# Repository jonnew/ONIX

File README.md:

# NOTE: This repository has been split into individual `onix-<project>` repos that are hosted on the [open-ephys github account](https://github.com/open-ephys). This repo has been archived.

[ONIX](https://open-ephys.github.io/onix-docs/index.html) is a collection
of [ONI](https://github.com/jonnew/ONI)-compatible hardware and API
for serialized, very-high channel count, closed-loop electrophysiology. It is
an evolution of the first-generation hardware and software introduced in [Open
Ephys project](http://www.open-ephys.org/) and involves many of the same
developers.  The firmware and API are general purpose -- they can be used to
acquire from and control custom headstages with arbitrary arrangements of
sensors and actuators (e.g. cameras, bioamplifier chips, LED drivers, etc.) and
are not limited to the hardware in this repository.

__Documentation__ : https://open-ephys.github.io/onix-docs/index.html

__Citing this work__: 

1. Citing the paper

  - TODO

2. Citing the repository itself

  - 

## Features
- Follows the [ONI](https://github.com/jonnew/ONI)-specification for serialization protocols, host communication
  protocols, device drivers, and host API
- Firmware and API permit acquisition and control of arbitrary arrangements of
  sensors and actuators:

    - Headstages
    - Miniscopes
    - Photometry systems
    - Etc.

- Submillisecond round-trip communication from brain, through host PC's main
  memory, and back again.
- Headstages:

    - 64-, 128-, 256-channels of electrophysiology
    - Optogenetic stimulation
    - Electrical stimulation
    - 3D-pose measurement
    - Data, user control, and power via a tiny coaxial cable
    - Wireless communication

- Low-level API implementation
- High-level API language bindings and existing integration with [Open Ephys
  GUI](http://www.open-ephys.org/gui/) and [Bonsai](http://bonsai-rx.org/).
- Quality documentation and easy routes to purchasing assembled devices.

## Software

1. API: https://github.com/jonnew/liboni
2. Bonsai package: coming soon
3. Open Ephys GUI plugin: coming soon

## Hardware

### [eib-64](eib-64/README.md)
64 Channel electrode interface board. Designed for small rodent tetrode
electrophysiology. Works with [headstage-64](./headstage-64/README.md).

### [eib-128](eib-128/README.md)
128 Channel electrode interface board. Designed for large rodent tetrode
electrophysiology. Works with [headstage-256](./headstage-256/README.md).

### [eib-256](eib-256/README.md)
256 Channel electrode interface board. Designed for large rodent tetrode
electrophysiology. Works with [headstage-256](./headstage-256/README.md).

### [headstage-64](headstage-64/README.md)
Serialized, multifunction headstage for small rodents. Supports 64 channels.
Designed to interface with [eib-64](./eib-64/README.md).

### [headstage-256](headstage-256/README.md)
Serialized, multifunction headstage for large rodents. Supports both 128 or 256
channels. Designed to interface with [eib-128](./eib-128/README.md) or
[eib-256](./eib-256/README.md)

### [fmc-host](fmc-host/README.md)
Base board for facilitating PCIe communication, via FMC compatiable and
PCIe-capable FPGA based board (e.g. [Numato Lab
Nereid](https://numato.com/product/nereid-kintex-7-pci-express-fpga-development-board).
This board plugs into the FMC connector on the base board. It provides
communication with one headstage and lots of other analog and digital IO.

### [analog-io-breakout](analog-io-breakout/README.md)
Passive breakout board for acquiring and generating analog signals through BNC,
SMA, ribbon, or straight wire connections. Plugs into fmc-host using a 26-pin
shrunk delta ribbon cable.

### [nanoz-adapter-64](./nanoz-adapter-64/README.md)
Adapter to interface eib-64 with the popular
[nanoZ](http://www.white-matter.com/nanoz/) electrode impedance tester and
plating device.

### [nanoz-adapter-128-256](./nanoz-adapter-128-256/README.md)
Multiplexed adapter to interface eib-128 and eib-256 with the popular
[nanoZ](http://www.white-matter.com/nanoz/) electrode impedance tester and
plating device.

### [test-board-64](./test-board-64)
Test board for headstage-64. Allows injecting simulated biopotentials into
headstage modules via a selectable passive attenuator. Provides LEDs and
simulated electrical loads for optical and electrical stimulation.

### [test-board-128-256](./test-board-128-256)
Test board for headstage, and headstage-256 modules. Allows injecting simulated
biopotentials into headstage modules via a selectable passive attenuator.
Provides LEDs and simulated electrical loads for optical and electrical
stimulation.

### [headstage-programmer](headstage-programmer/README.md)
JTAG breakout for the [Intel USB Blaster 2](https://www.digikey.com/short/qqw7hm)
used to program the headstages' MAX10 FPGA.

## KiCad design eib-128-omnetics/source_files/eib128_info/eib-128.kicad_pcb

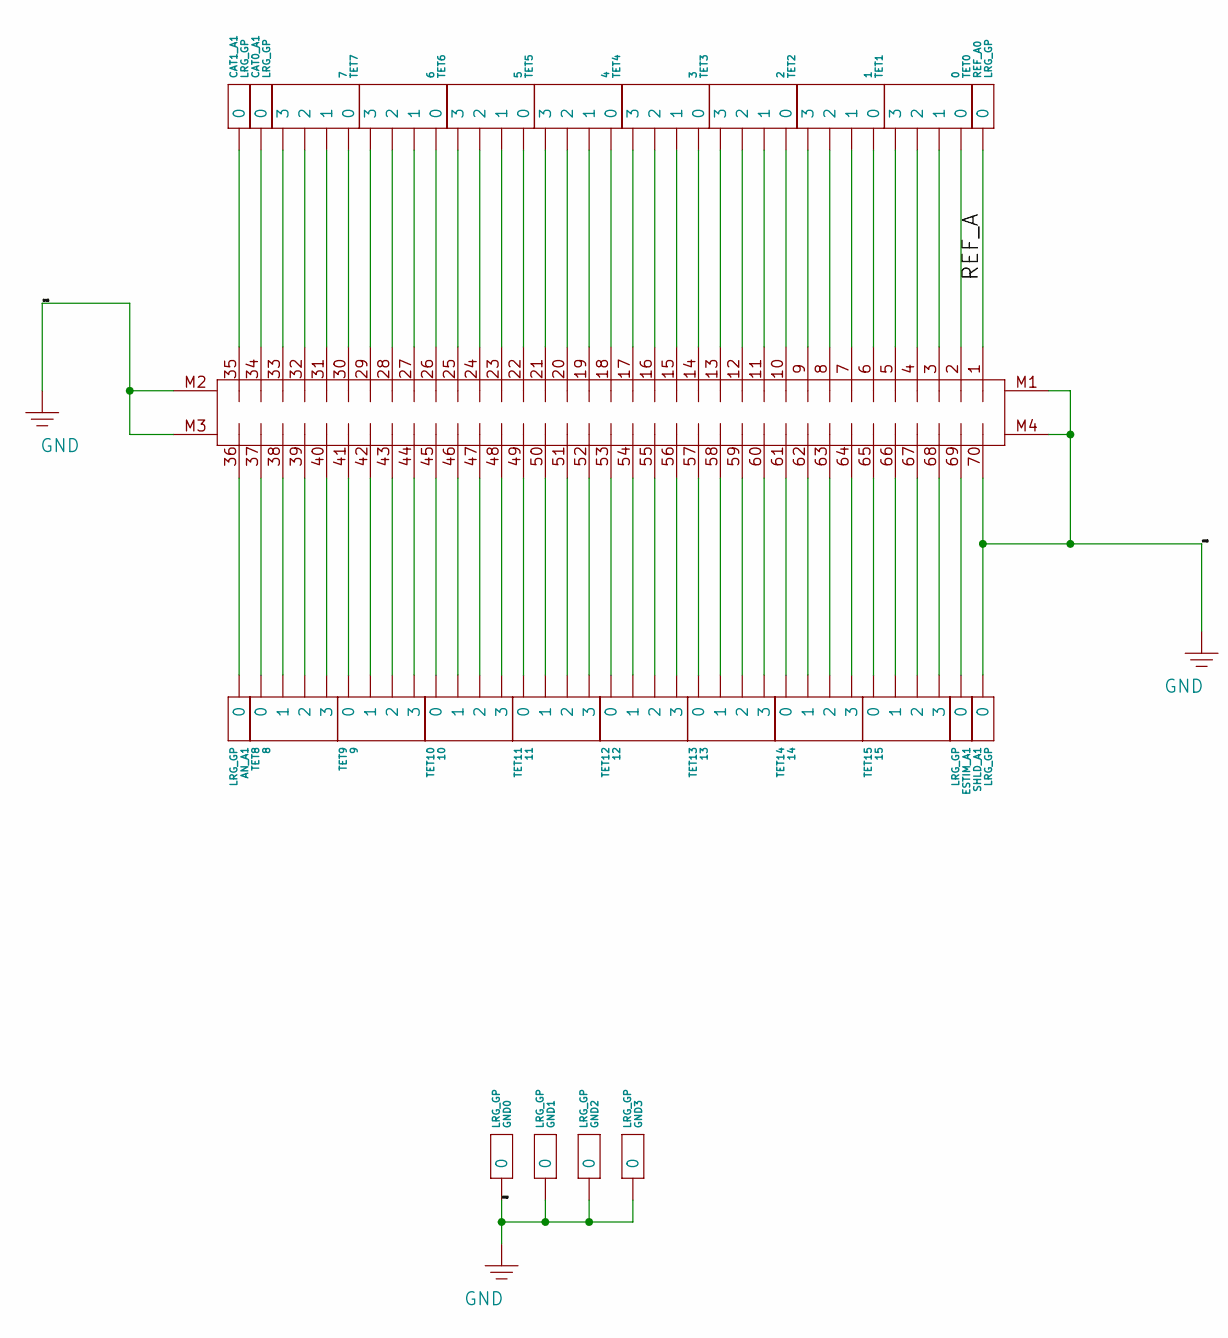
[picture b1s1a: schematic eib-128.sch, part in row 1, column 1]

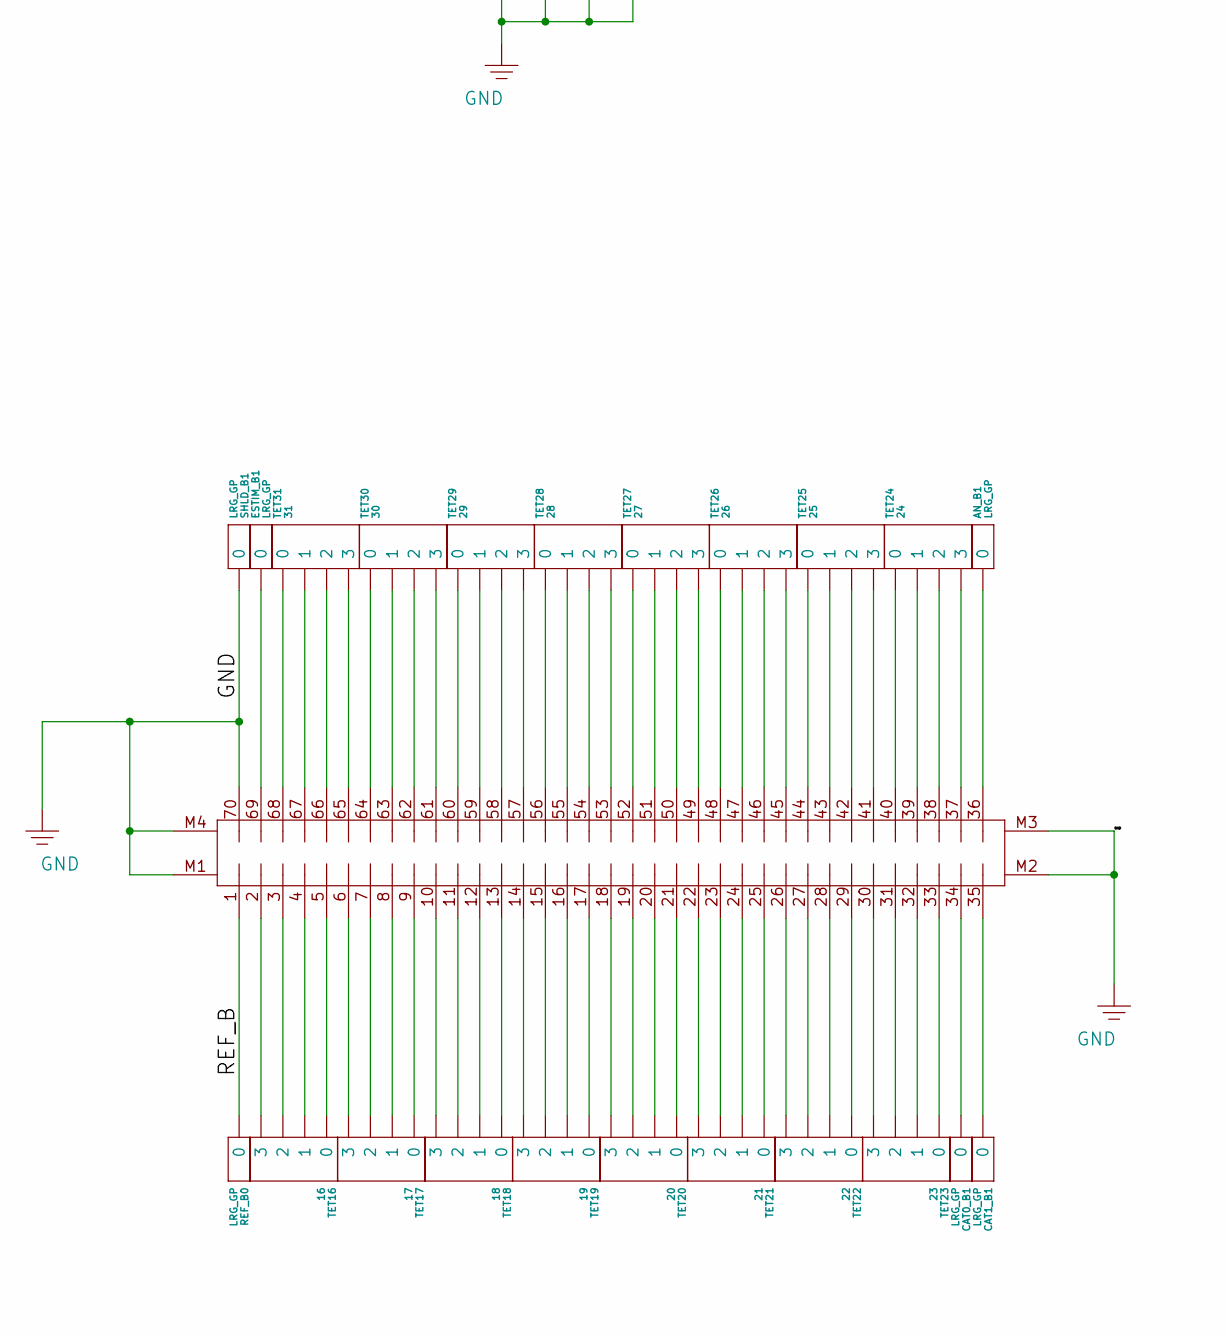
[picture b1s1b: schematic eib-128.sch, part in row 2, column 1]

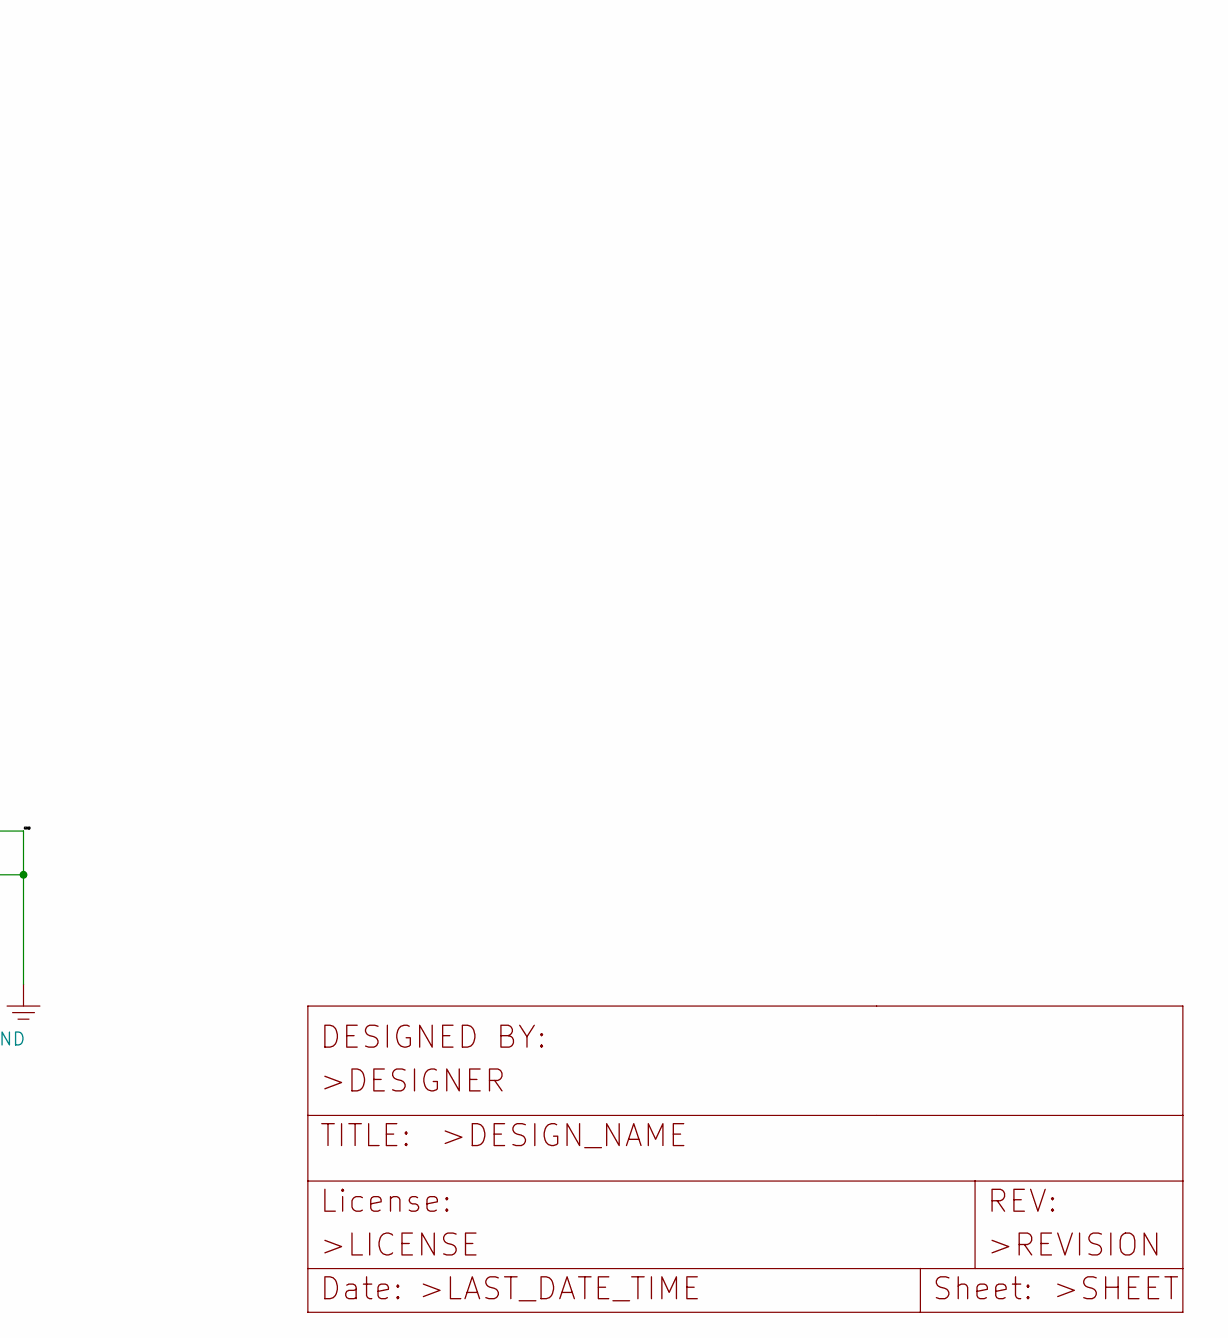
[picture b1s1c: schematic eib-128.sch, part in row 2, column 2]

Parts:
A1: DF40HEAD; DF40-70HEAD
AN_A1: LRG_GP; GOLDPIN_0.5ID_0.7OD
AN_B1: LRG_GP; GOLDPIN_0.5ID_0.7OD
B1: DF40HEAD; DF40-70HEAD
CAT0_A1, CAT0_B1, CAT1_A1, CAT1_B1: LRG_GP; GOLDPIN_0.5ID_0.7OD
ESTIM_A1: LRG_GP; GOLDPIN_0.5ID_0.7OD
ESTIM_B1: LRG_GP; GOLDPIN_0.5ID_0.7OD
GND0, GND1, GND2, GND3: LRG_GP; GOLDPIN_0.5ID_0.7OD
REF_A0: LRG_GP; GOLDPIN_0.5ID_0.7OD
REF_B0: LRG_GP; GOLDPIN_0.5ID_0.7OD
SHLD_A1: LRG_GP; GOLDPIN_0.5ID_0.7OD
SHLD_B1: LRG_GP; GOLDPIN_0.5ID_0.7OD
TET0: 0; TETRODE_128_0.5ID_0.7OD
TET1: 1; TETRODE_128_0.5ID_0.7OD
TET2: 2; TETRODE_128_0.5ID_0.7OD
TET3: 3; TETRODE_128_0.5ID_0.7OD
TET4: 4; TETRODE_128_0.5ID_0.7OD
TET5: 5; TETRODE_128_0.5ID_0.7OD
TET6: 6; TETRODE_128_0.5ID_0.7OD
TET7: 7; TETRODE_128_0.5ID_0.7OD
TET8: 8; TETRODE_128_0.5ID_0.7OD
TET9: 9; TETRODE_128_0.5ID_0.7OD
TET10: 10; TETRODE_128_0.5ID_0.7OD
TET11: 11; TETRODE_128_0.5ID_0.7OD
TET12: 12; TETRODE_128_0.5ID_0.7OD
TET13: 13; TETRODE_128_0.5ID_0.7OD
TET14: 14; TETRODE_128_0.5ID_0.7OD
TET15: 15; TETRODE_128_0.5ID_0.7OD
TET16: 16; TETRODE_128_0.5ID_0.7OD
TET17: 17; TETRODE_128_0.5ID_0.7OD
TET18: 18; TETRODE_128_0.5ID_0.7OD
TET19: 19; TETRODE_128_0.5ID_0.7OD
TET20: 20; TETRODE_128_0.5ID_0.7OD
TET21: 21; TETRODE_128_0.5ID_0.7OD
TET22: 22; TETRODE_128_0.5ID_0.7OD
TET23: 23; TETRODE_128_0.5ID_0.7OD
TET24: 24; TETRODE_128_0.5ID_0.7OD
TET25: 25; TETRODE_128_0.5ID_0.7OD
TET26: 26; TETRODE_128_0.5ID_0.7OD
TET27: 27; TETRODE_128_0.5ID_0.7OD
TET28: 28; TETRODE_128_0.5ID_0.7OD
TET29: 29; TETRODE_128_0.5ID_0.7OD
TET30: 30; TETRODE_128_0.5ID_0.7OD
TET31: 31; TETRODE_128_0.5ID_0.7OD

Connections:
/REF_A: A1.1, REF_A0.P$1
/REF_B: B1.1, REF_B0.P$1
GND: A1.70, A1.M1, A1.M2, A1.M3, A1.M4, B1.70, B1.M1, B1.M2, B1.M3, B1.M4, GND0.P$1, GND1.P$1, GND2.P$1, GND3.P$1, SHLD_A1.P$1, SHLD_B1.P$1
unnamed: A1.2, TET0.0
unnamed: A1.3, TET0.1
unnamed: A1.4, TET0.2
unnamed: A1.5, TET0.3
unnamed: A1.6, TET1.0
unnamed: A1.7, TET1.1
unnamed: A1.8, TET1.2
unnamed: A1.9, TET1.3
unnamed: A1.10, TET2.0
unnamed: A1.11, TET2.1
unnamed: A1.12, TET2.2
unnamed: A1.13, TET2.3
unnamed: A1.14, TET3.0
unnamed: A1.15, TET3.1
unnamed: A1.16, TET3.2
unnamed: A1.17, TET3.3
unnamed: A1.18, TET4.0
unnamed: A1.19, TET4.1
unnamed: A1.20, TET4.2
unnamed: A1.21, TET4.3
unnamed: A1.22, TET5.0
unnamed: A1.23, TET5.1
unnamed: A1.24, TET5.2
unnamed: A1.25, TET5.3
unnamed: A1.26, TET6.0
unnamed: A1.27, TET6.1
unnamed: A1.28, TET6.2
unnamed: A1.29, TET6.3
unnamed: A1.30, TET7.0
unnamed: A1.31, TET7.1
unnamed: A1.32, TET7.2
unnamed: A1.33, TET7.3
unnamed: A1.34, CAT0_A1.P$1
unnamed: A1.35, CAT1_A1.P$1
unnamed: A1.36, AN_A1.P$1
unnamed: A1.37, TET8.0
unnamed: A1.38, TET8.1
unnamed: A1.39, TET8.2
unnamed: A1.40, TET8.3
unnamed: A1.41, TET9.0
unnamed: A1.42, TET9.1
unnamed: A1.43, TET9.2
unnamed: A1.44, TET9.3
unnamed: A1.45, TET10.0
unnamed: A1.46, TET10.1
unnamed: A1.47, TET10.2
unnamed: A1.48, TET10.3
unnamed: A1.49, TET11.0
unnamed: A1.50, TET11.1
unnamed: A1.51, TET11.2
unnamed: A1.52, TET11.3
unnamed: A1.53, TET12.0
unnamed: A1.54, TET12.1
unnamed: A1.55, TET12.2
unnamed: A1.56, TET12.3
unnamed: A1.57, TET13.0
unnamed: A1.58, TET13.1
unnamed: A1.59, TET13.2
unnamed: A1.60, TET13.3
unnamed: A1.61, TET14.0
unnamed: A1.62, TET14.1
unnamed: A1.63, TET14.2
unnamed: A1.64, TET14.3
unnamed: A1.65, TET15.0
unnamed: A1.66, TET15.1
unnamed: A1.67, TET15.2
unnamed: A1.68, TET15.3
unnamed: A1.69, ESTIM_A1.P$1
unnamed: AN_B1.P$1, B1.36
unnamed: B1.2, TET16.3
unnamed: B1.3, TET16.2
unnamed: B1.4, TET16.1
unnamed: B1.5, TET16.0
unnamed: B1.6, TET17.3
unnamed: B1.7, TET17.2
unnamed: B1.8, TET17.1
unnamed: B1.9, TET17.0
unnamed: B1.10, TET18.3
unnamed: B1.11, TET18.2
unnamed: B1.12, TET18.1
unnamed: B1.13, TET18.0
unnamed: B1.14, TET19.3
unnamed: B1.15, TET19.2
unnamed: B1.16, TET19.1
unnamed: B1.17, TET19.0
unnamed: B1.18, TET20.3
unnamed: B1.19, TET20.2
unnamed: B1.20, TET20.1
unnamed: B1.21, TET20.0
unnamed: B1.22, TET21.3
unnamed: B1.23, TET21.2
unnamed: B1.24, TET21.1
unnamed: B1.25, TET21.0
unnamed: B1.26, TET22.3
unnamed: B1.27, TET22.2
unnamed: B1.28, TET22.1
unnamed: B1.29, TET22.0
unnamed: B1.30, TET23.3
unnamed: B1.31, TET23.2
unnamed: B1.32, TET23.1
unnamed: B1.33, TET23.0
unnamed: B1.34, CAT0_B1.P$1
unnamed: B1.35, CAT1_B1.P$1
unnamed: B1.37, TET24.3
unnamed: B1.38, TET24.2
unnamed: B1.39, TET24.1
unnamed: B1.40, TET24.0
unnamed: B1.41, TET25.3
unnamed: B1.42, TET25.2
unnamed: B1.43, TET25.1
unnamed: B1.44, TET25.0
unnamed: B1.45, TET26.3
unnamed: B1.46, TET26.2
unnamed: B1.47, TET26.1
unnamed: B1.48, TET26.0
unnamed: B1.49, TET27.3
unnamed: B1.50, TET27.2
unnamed: B1.51, TET27.1
unnamed: B1.52, TET27.0
unnamed: B1.53, TET28.3
unnamed: B1.54, TET28.2
unnamed: B1.55, TET28.1
unnamed: B1.56, TET28.0
unnamed: B1.57, TET29.3
unnamed: B1.58, TET29.2
unnamed: B1.59, TET29.1
unnamed: B1.60, TET29.0
unnamed: B1.61, TET30.3
unnamed: B1.62, TET30.2
unnamed: B1.63, TET30.1
unnamed: B1.64, TET30.0
unnamed: B1.65, TET31.3
unnamed: B1.66, TET31.2
unnamed: B1.67, TET31.1
unnamed: B1.68, TET31.0
unnamed: B1.69, ESTIM_B1.P$1

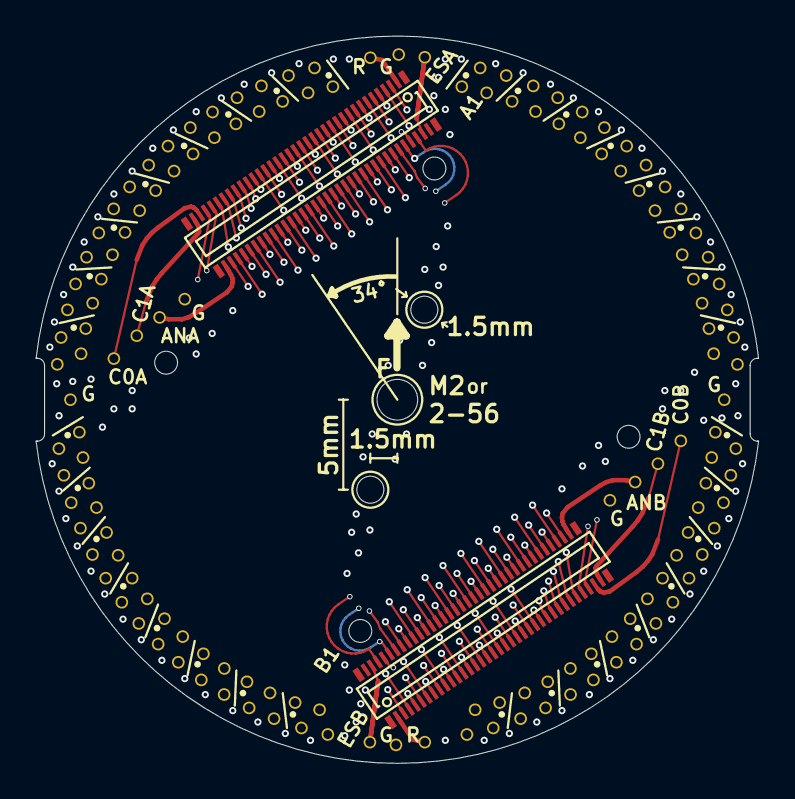
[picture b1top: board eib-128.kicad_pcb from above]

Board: 4 copper layers, 40.1 x 40.4 mm, 55 parts (0 on the bottom side), 139 nets.

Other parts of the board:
@HOLE0, @HOLE1, @HOLE2, @HOLE3: (no value)
U$1: EIB_MOUNT_A

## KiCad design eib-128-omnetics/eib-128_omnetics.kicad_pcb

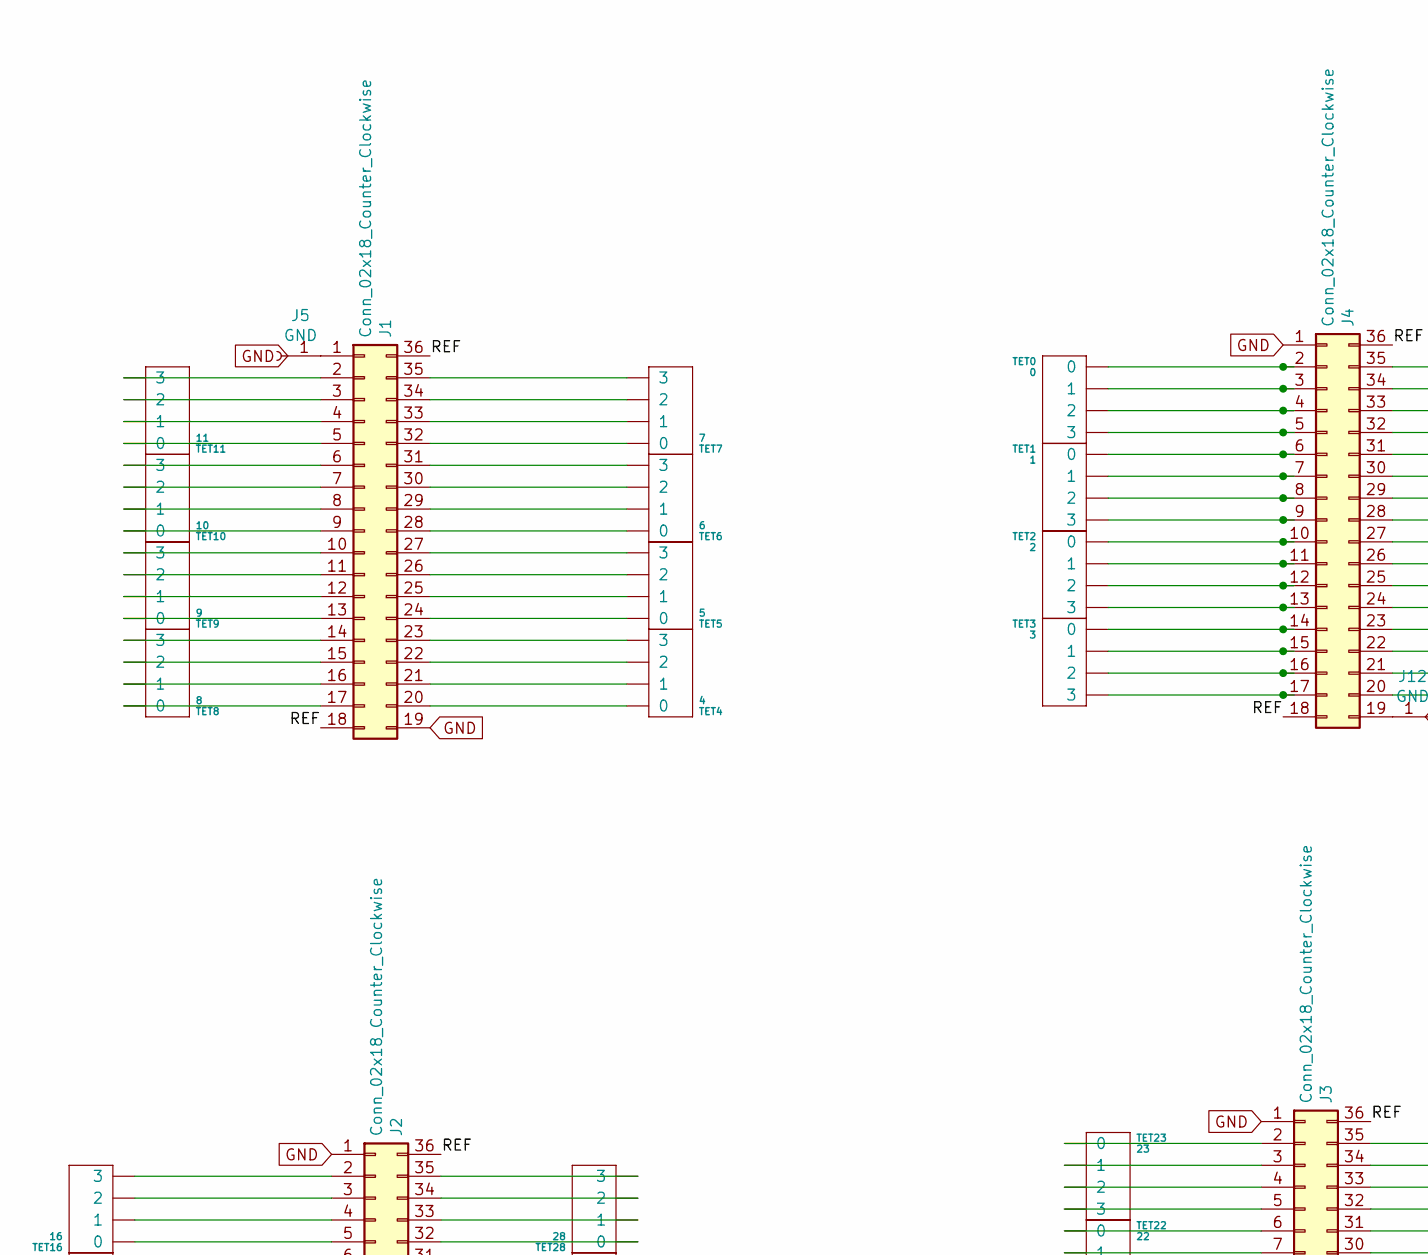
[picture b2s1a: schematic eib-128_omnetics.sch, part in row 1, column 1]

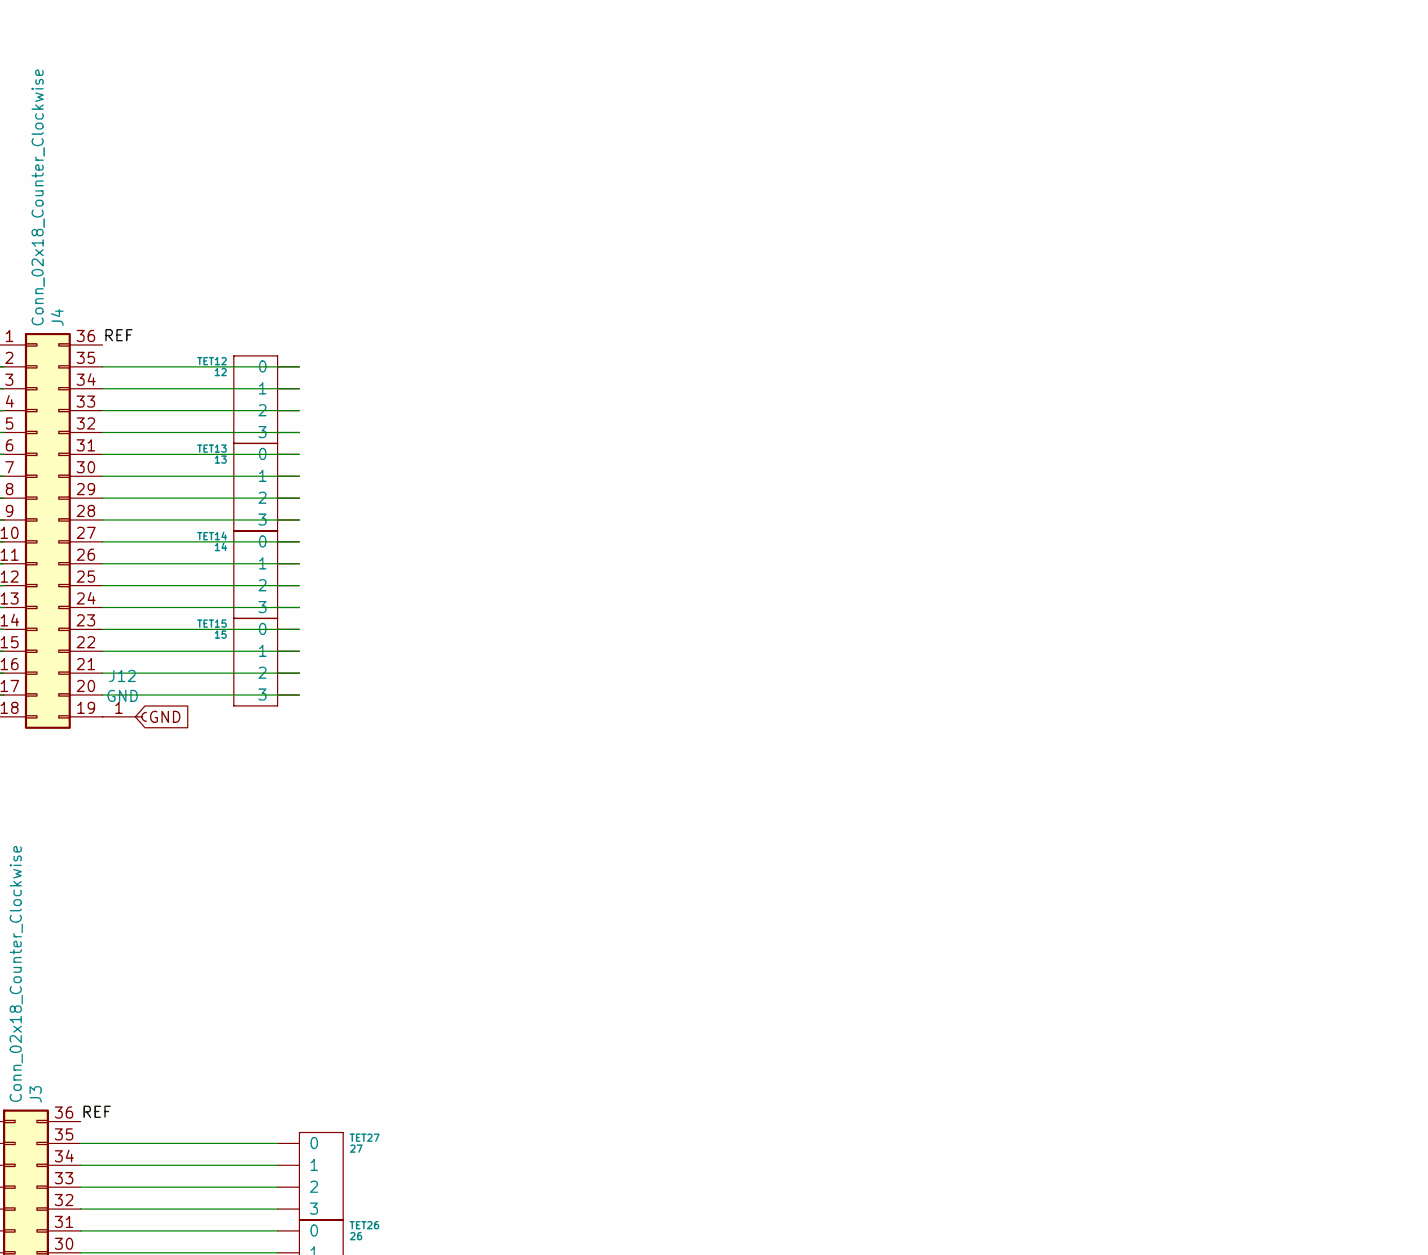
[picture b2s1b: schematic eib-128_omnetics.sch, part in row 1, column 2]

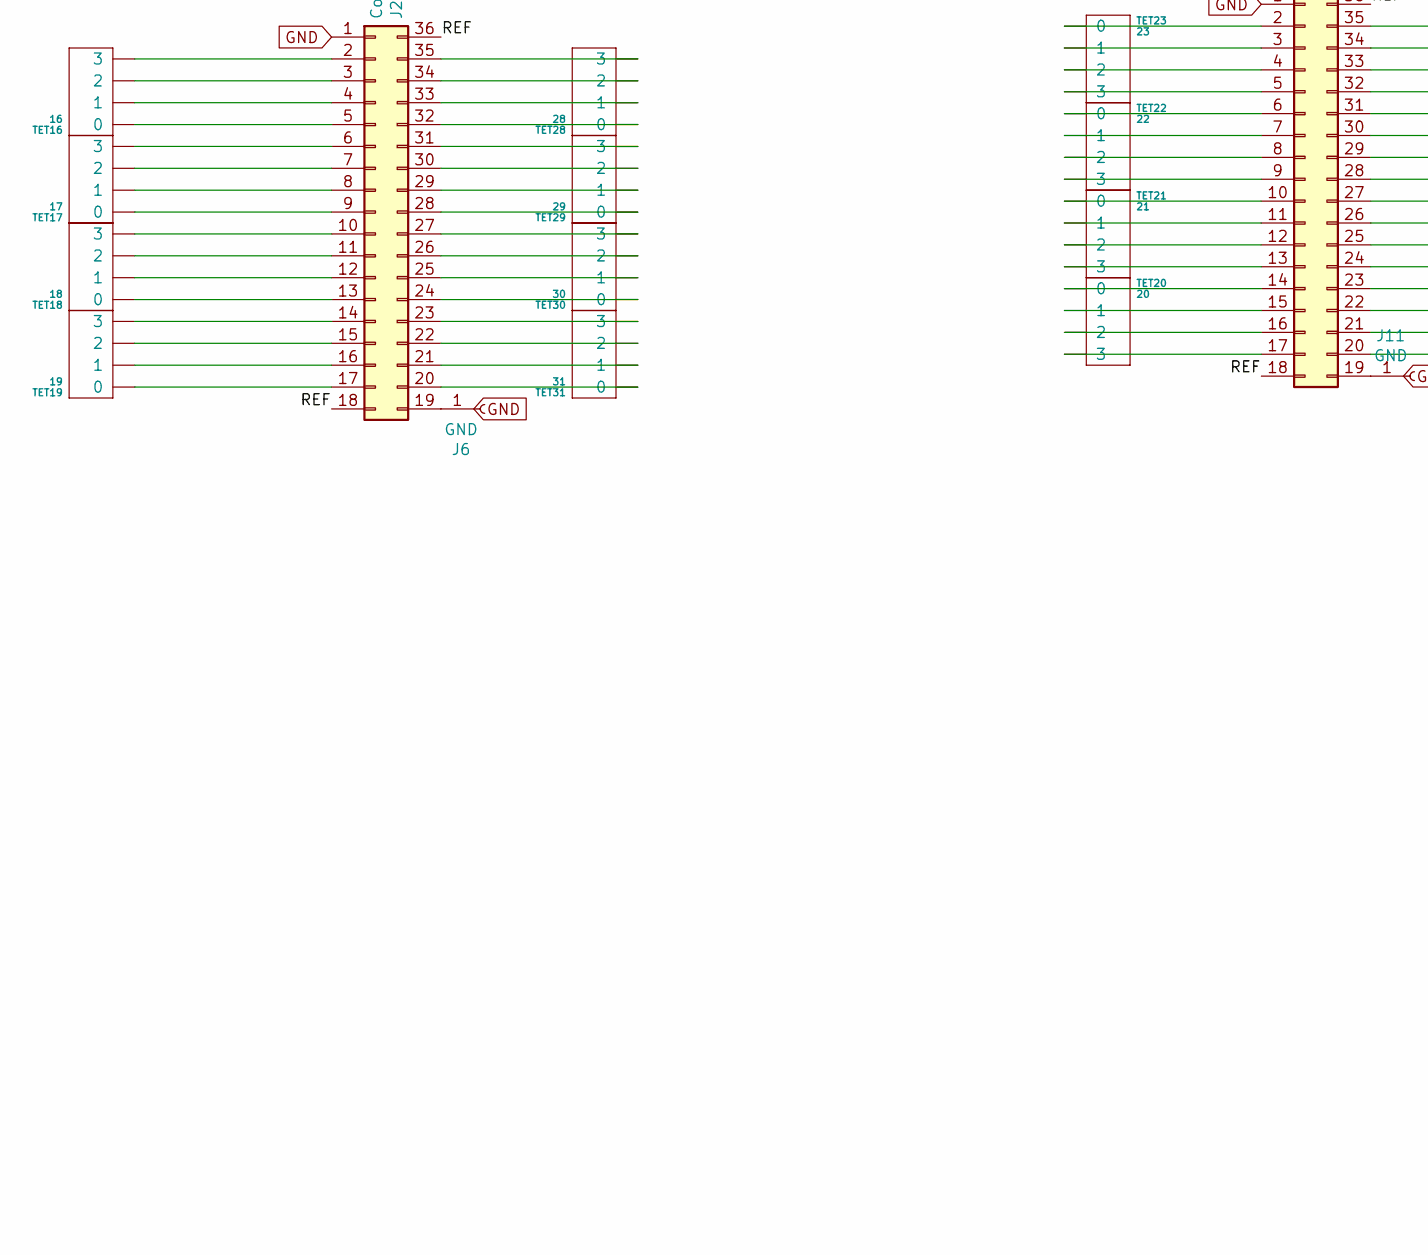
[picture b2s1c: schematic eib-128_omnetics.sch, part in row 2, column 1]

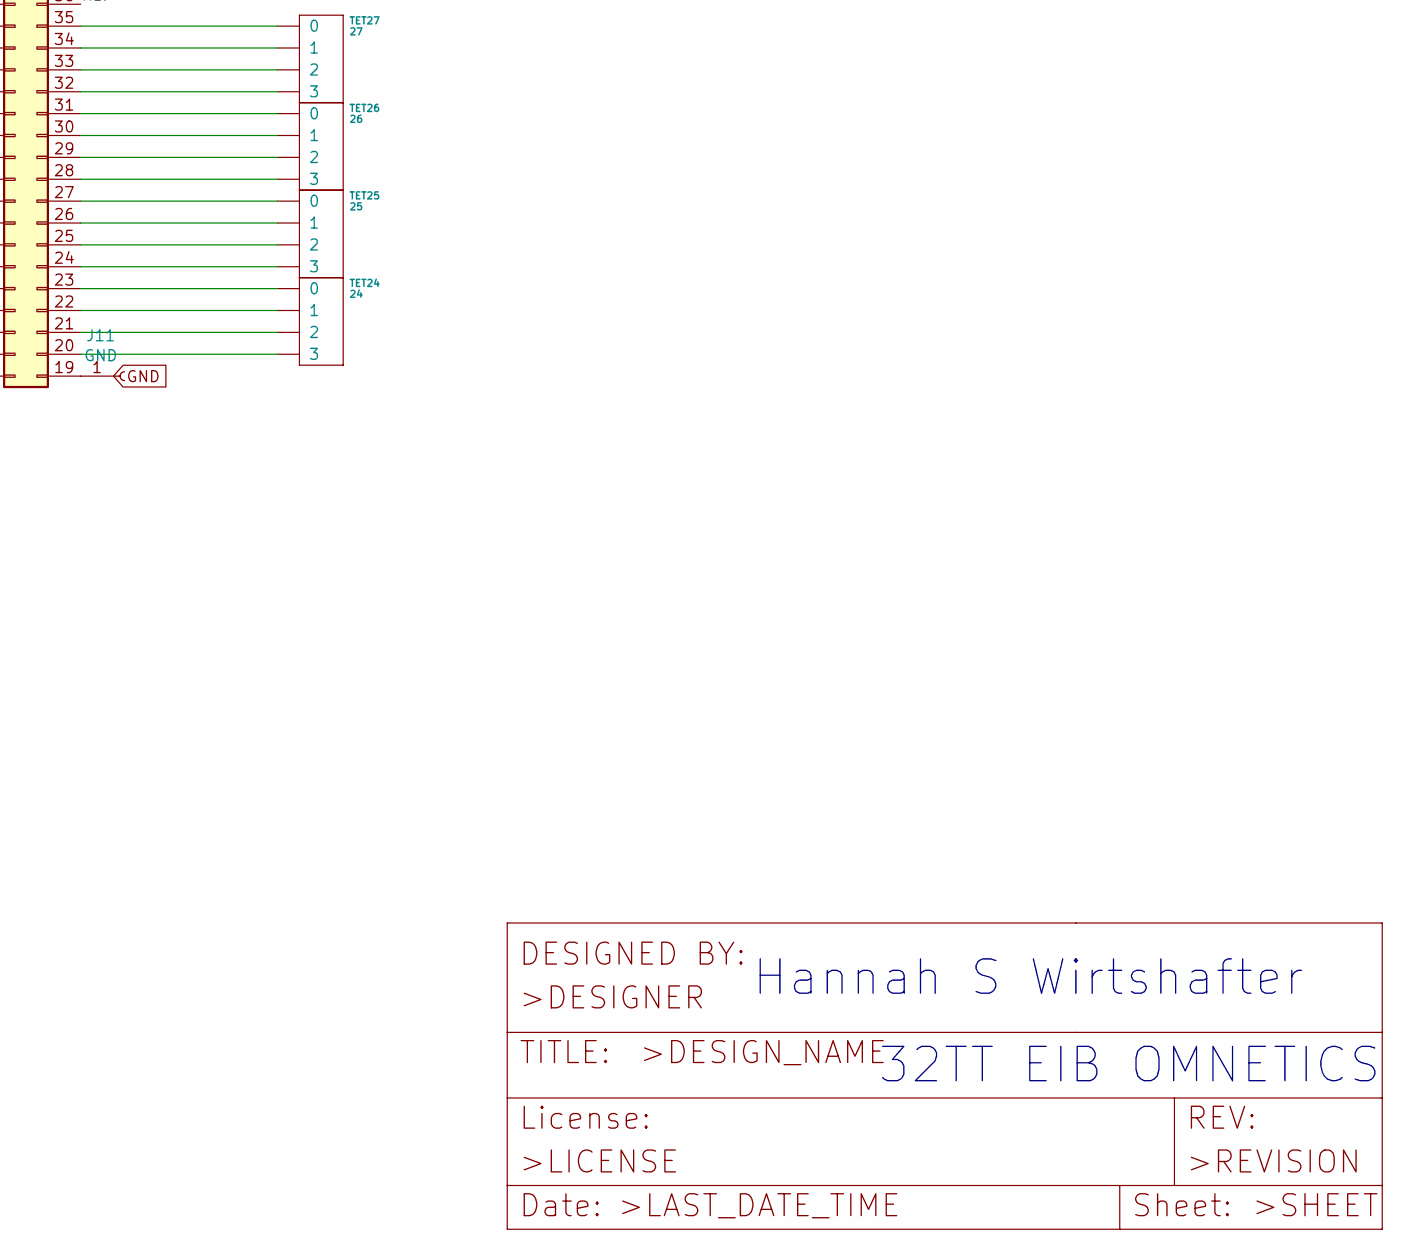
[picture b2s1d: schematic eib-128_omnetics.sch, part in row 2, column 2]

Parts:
J1, J2, J3, J4: Conn_02x18_Counter_Clockwise; NPD-36-VV-GS
J5, J6, J11, J12: GND; GOLDPIN_0.5ID_0.7OD
TET0: 0; TETRODE_128_0.5ID_0.7OD
TET1: 1; TETRODE_128_0.5ID_0.7OD
TET2: 2; TETRODE_128_0.5ID_0.7OD
TET3: 3; TETRODE_128_0.5ID_0.7OD
TET4: 4; TETRODE_128_0.5ID_0.7OD
TET5: 5; TETRODE_128_0.5ID_0.7OD
TET6: 6; TETRODE_128_0.5ID_0.7OD
TET7: 7; TETRODE_128_0.5ID_0.7OD
TET8: 8; TETRODE_128_0.5ID_0.7OD
TET9: 9; TETRODE_128_0.5ID_0.7OD
TET10: 10; TETRODE_128_0.5ID_0.7OD
TET11: 11; TETRODE_128_0.5ID_0.7OD
TET12: 12; TETRODE_128_0.5ID_0.7OD
TET13: 13; TETRODE_128_0.5ID_0.7OD
TET14: 14; TETRODE_128_0.5ID_0.7OD
TET15: 15; TETRODE_128_0.5ID_0.7OD
TET16: 16; TETRODE_128_0.5ID_0.7OD
TET17: 17; TETRODE_128_0.5ID_0.7OD
TET18: 18; TETRODE_128_0.5ID_0.7OD
TET19: 19; TETRODE_128_0.5ID_0.7OD
TET20: 20; TETRODE_128_0.5ID_0.7OD
TET21: 21; TETRODE_128_0.5ID_0.7OD
TET22: 22; TETRODE_128_0.5ID_0.7OD
TET23: 23; TETRODE_128_0.5ID_0.7OD
TET24: 24; TETRODE_128_0.5ID_0.7OD
TET25: 25; TETRODE_128_0.5ID_0.7OD
TET26: 26; TETRODE_128_0.5ID_0.7OD
TET27: 27; TETRODE_128_0.5ID_0.7OD
TET28: 28; TETRODE_128_0.5ID_0.7OD
TET29: 29; TETRODE_128_0.5ID_0.7OD
TET30: 30; TETRODE_128_0.5ID_0.7OD
TET31: 31; TETRODE_128_0.5ID_0.7OD

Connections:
/REF: J1.18, J1.36, J2.18, J2.36, J3.18, J3.36, J4.18, J4.36
GND: J1.19, J2.1, J3.1, J4.1
unnamed: J1.1, J5.1
unnamed: J1.2, TET11.3
unnamed: J1.3, TET11.2
unnamed: J1.4, TET11.1
unnamed: J1.5, TET11.0
unnamed: J1.6, TET10.3
unnamed: J1.7, TET10.2
unnamed: J1.8, TET10.1
unnamed: J1.9, TET10.0
unnamed: J1.10, TET9.3
unnamed: J1.11, TET9.2
unnamed: J1.12, TET9.1
unnamed: J1.13, TET9.0
unnamed: J1.14, TET8.3
unnamed: J1.15, TET8.2
unnamed: J1.16, TET8.1
unnamed: J1.17, TET8.0
unnamed: J1.20, TET4.0
unnamed: J1.21, TET4.1
unnamed: J1.22, TET4.2
unnamed: J1.23, TET4.3
unnamed: J1.24, TET5.0
unnamed: J1.25, TET5.1
unnamed: J1.26, TET5.2
unnamed: J1.27, TET5.3
unnamed: J1.28, TET6.0
unnamed: J1.29, TET6.1
unnamed: J1.30, TET6.2
unnamed: J1.31, TET6.3
unnamed: J1.32, TET7.0
unnamed: J1.33, TET7.1
unnamed: J1.34, TET7.2
unnamed: J1.35, TET7.3
unnamed: J2.2, TET16.3
unnamed: J2.3, TET16.2
unnamed: J2.4, TET16.1
unnamed: J2.5, TET16.0
unnamed: J2.6, TET17.3
unnamed: J2.7, TET17.2
unnamed: J2.8, TET17.1
unnamed: J2.9, TET17.0
unnamed: J2.10, TET18.3
unnamed: J2.11, TET18.2
unnamed: J2.12, TET18.1
unnamed: J2.13, TET18.0
unnamed: J2.14, TET19.3
unnamed: J2.15, TET19.2
unnamed: J2.16, TET19.1
unnamed: J2.17, TET19.0
unnamed: J2.19, J6.1
unnamed: J2.20, TET31.0
unnamed: J2.21, TET31.1
unnamed: J2.22, TET31.2
unnamed: J2.23, TET31.3
unnamed: J2.24, TET30.0
unnamed: J2.25, TET30.1
unnamed: J2.26, TET30.2
unnamed: J2.27, TET30.3
unnamed: J2.28, TET29.0
unnamed: J2.29, TET29.1
unnamed: J2.30, TET29.2
unnamed: J2.31, TET29.3
unnamed: J2.32, TET28.0
unnamed: J2.33, TET28.1
unnamed: J2.34, TET28.2
unnamed: J2.35, TET28.3
unnamed: J3.2, TET23.0
unnamed: J3.3, TET23.1
unnamed: J3.4, TET23.2
unnamed: J3.5, TET23.3
unnamed: J3.6, TET22.0
unnamed: J3.7, TET22.1
unnamed: J3.8, TET22.2
unnamed: J3.9, TET22.3
unnamed: J3.10, TET21.0
unnamed: J3.11, TET21.1
unnamed: J3.12, TET21.2
unnamed: J3.13, TET21.3
unnamed: J3.14, TET20.0
unnamed: J3.15, TET20.1
unnamed: J3.16, TET20.2
unnamed: J3.17, TET20.3
unnamed: J3.20, TET24.3
unnamed: J3.21, TET24.2
unnamed: J3.22, TET24.1
unnamed: J3.23, TET24.0
unnamed: J3.24, TET25.3
unnamed: J3.25, TET25.2
unnamed: J3.26, TET25.1
unnamed: J3.27, TET25.0
unnamed: J3.28, TET26.3
unnamed: J3.29, TET26.2
unnamed: J3.30, TET26.1
unnamed: J3.31, TET26.0
unnamed: J3.32, TET27.3
unnamed: J3.33, TET27.2
unnamed: J3.34, TET27.1
unnamed: J3.35, TET27.0
unnamed: J4.2, TET0.0
unnamed: J4.3, TET0.1
unnamed: J4.4, TET0.2
unnamed: J4.5, TET0.3
unnamed: J4.6, TET1.0
unnamed: J4.7, TET1.1
unnamed: J4.8, TET1.2
unnamed: J4.9, TET1.3
unnamed: J4.10, TET2.0
unnamed: J4.11, TET2.1
unnamed: J4.12, TET2.2
unnamed: J4.13, TET2.3
unnamed: J4.14, TET3.0
unnamed: J4.15, TET3.1
unnamed: J4.16, TET3.2
unnamed: J4.17, TET3.3
unnamed: J4.20, TET15.3
unnamed: J4.21, TET15.2
unnamed: J4.22, TET15.1
unnamed: J4.23, TET15.0
unnamed: J4.24, TET14.3
unnamed: J4.25, TET14.2
unnamed: J4.26, TET14.1
unnamed: J4.27, TET14.0
unnamed: J4.28, TET13.3
unnamed: J4.29, TET13.2
unnamed: J4.30, TET13.1
unnamed: J4.31, TET13.0
unnamed: J4.32, TET12.3
unnamed: J4.33, TET12.2
unnamed: J4.34, TET12.1
unnamed: J4.35, TET12.0
unnamed: J3.19, J11.1
unnamed: J4.19, J12.1

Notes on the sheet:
Hannah S Wirtshafter
32TT EIB OMNETICS

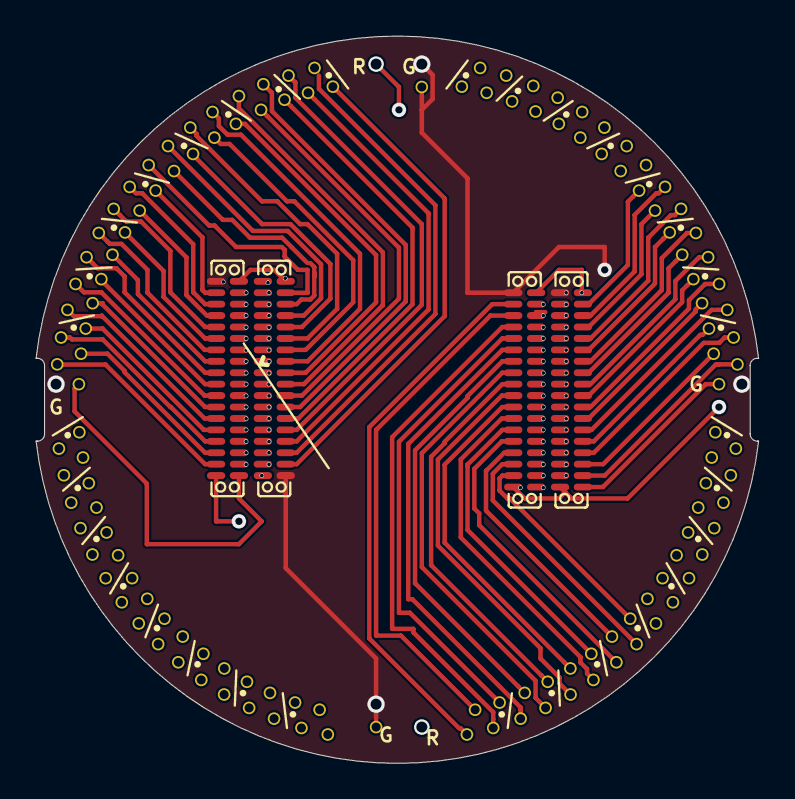
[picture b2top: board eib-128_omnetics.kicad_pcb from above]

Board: 4 copper layers, 40.1 x 40.4 mm, 40 parts (0 on the bottom side), 134 nets.

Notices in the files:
eib-128-omnetics/source_files/eib128_info/eib-128.kicad_pcb:
CERN OHL 1.2
eib-128-omnetics/source_files/omentics_info/eib-64-intan-hs v1.0 revA.sch:
LICENSE: CERN OHL v1.2
fmc-host/revisions/rev-1.4/fmc-host/fmc-host.kicad_pcb:
CERN OHL v1.2
